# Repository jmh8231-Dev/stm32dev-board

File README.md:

# STM32F407ZETx 개발보드

**STM32F407ZETx** MCU를 중심으로 DS3231(RTC), VS1003(Audio Codec), microSD(4‑bit SDIO),
SN65HVD230(CAN), USB‑to‑TTL, **DP83848(Ethernet PHY)** 등을 온보드로 구성하고
대형 **브레드보드**와 12 V/5 V/3.3 V 전원 및 **SPI/I²C/PWM 헤더**를 둘러 배치한 실습·프로토타이핑 전용 보드입니다.

---

## 1. 보드 하이라이트

- **MCU**: STM32F407ZETx (LQFP‑144), 8/16 MHz 외부 크리스털, ST‑LINK 20‑핀
- **전원 트리**: 12 V DC 잭 입력 → **LM2596‑5 V**, **LM2596‑3.3 V**
  - 브레드보드 주변에 **12 V / 5 V / 3.3 V 전원 핀** 다수 제공
- **통신/네트워킹**
  - **DP83848** 10/100 Ethernet PHY + RJ45
  - **SN65HVD230** CAN 트랜시버
  - **USB‑to‑TTL**(FT232RL 계열)
- **저장/오디오/시간**
  - **microSD(4‑bit SDIO)**, **VS1003** 오디오 코덱, **DS3231 RTC**
- **사용자 입출력**
  - **20×4 캐릭터 LCD(CLCD2004)** 장착 영역(백라이트 제어)
  - **브레드보드** 장착(보드 일체), 주변에 **SPI/I²C/PWM 헤더** 배치
  - 가변저항/버튼/버저 등 실습용 풋프린트
- **확장성**: 각 인터페이스에 테스트 포인트/점퍼 제공

---

## 2. 주변장치 매핑 요약

| 기능 | 부품/모듈 | 인터페이스 | 비고 |
|---|---|---|---|
| Ethernet | TI **DP83848** | RMII/MII | RJ45, 링크 LED |
| CAN | TI **SN65HVD230** | CAN | 종단저항 점퍼 |
| Audio | **VS1003** | SPI / I²S | Sine test 지원 |
| Storage | microSD | **4‑bit SDIO** | 카드 감지/쓰기보호 |
| RTC | **DS3231** | I²C | 코인셀 백업 |
| USB‑UART | **FT232RL** | USB‑CDC | 부트 로그/쉘 |
| LCD | **CLCD2004** | 병렬 | 백라이트 제어 |
| Breadboard | 1열×2면 | — | SPI/I²C/PWM/전원 배치 |

---

## 3. 빠른 시작

1) 12 V 어댑터 연결 → 전원 LED 확인  
2) ST‑LINK 연결 후 예제 펌웨어 다운로드  
3) **Ethernet → CAN → SDIO → I²C(DS3231) → SPI(VS1003)** 순으로 브링업  
4) 브레드보드에 센서/액추에이터 연결 → SPI/I²C/PWM 헤더로 배선  
5) LCD 장착 후 상태/메뉴 표시 구현

---

## 4. 브링업 체크리스트

- **전원 리플/부하 테스트**(5 V/3.3 V)
- **SDIO 4‑bit**: HS 모드, 카드 감지/쓰기 보호 입력 확인
- **RMII/MII**: DP83848 링크/속도/MDIO 확인
- **CAN**: 루프백 → 실선 통신, 종단저항 설정
- **RTC**: DS3231 1 Hz/32 kHz, 온도 보정 레지스터 확인
- **VS1003**: SCI 레지스터 접근, sine test

---

## 5. 파일 트리

```text
stm32f407-devboard/
├─ README.md
└─ docs/
   └─ images/
      ├─ render_top.png
      ├─ pcb_layout.png
      └─ photo_top.jpg
```

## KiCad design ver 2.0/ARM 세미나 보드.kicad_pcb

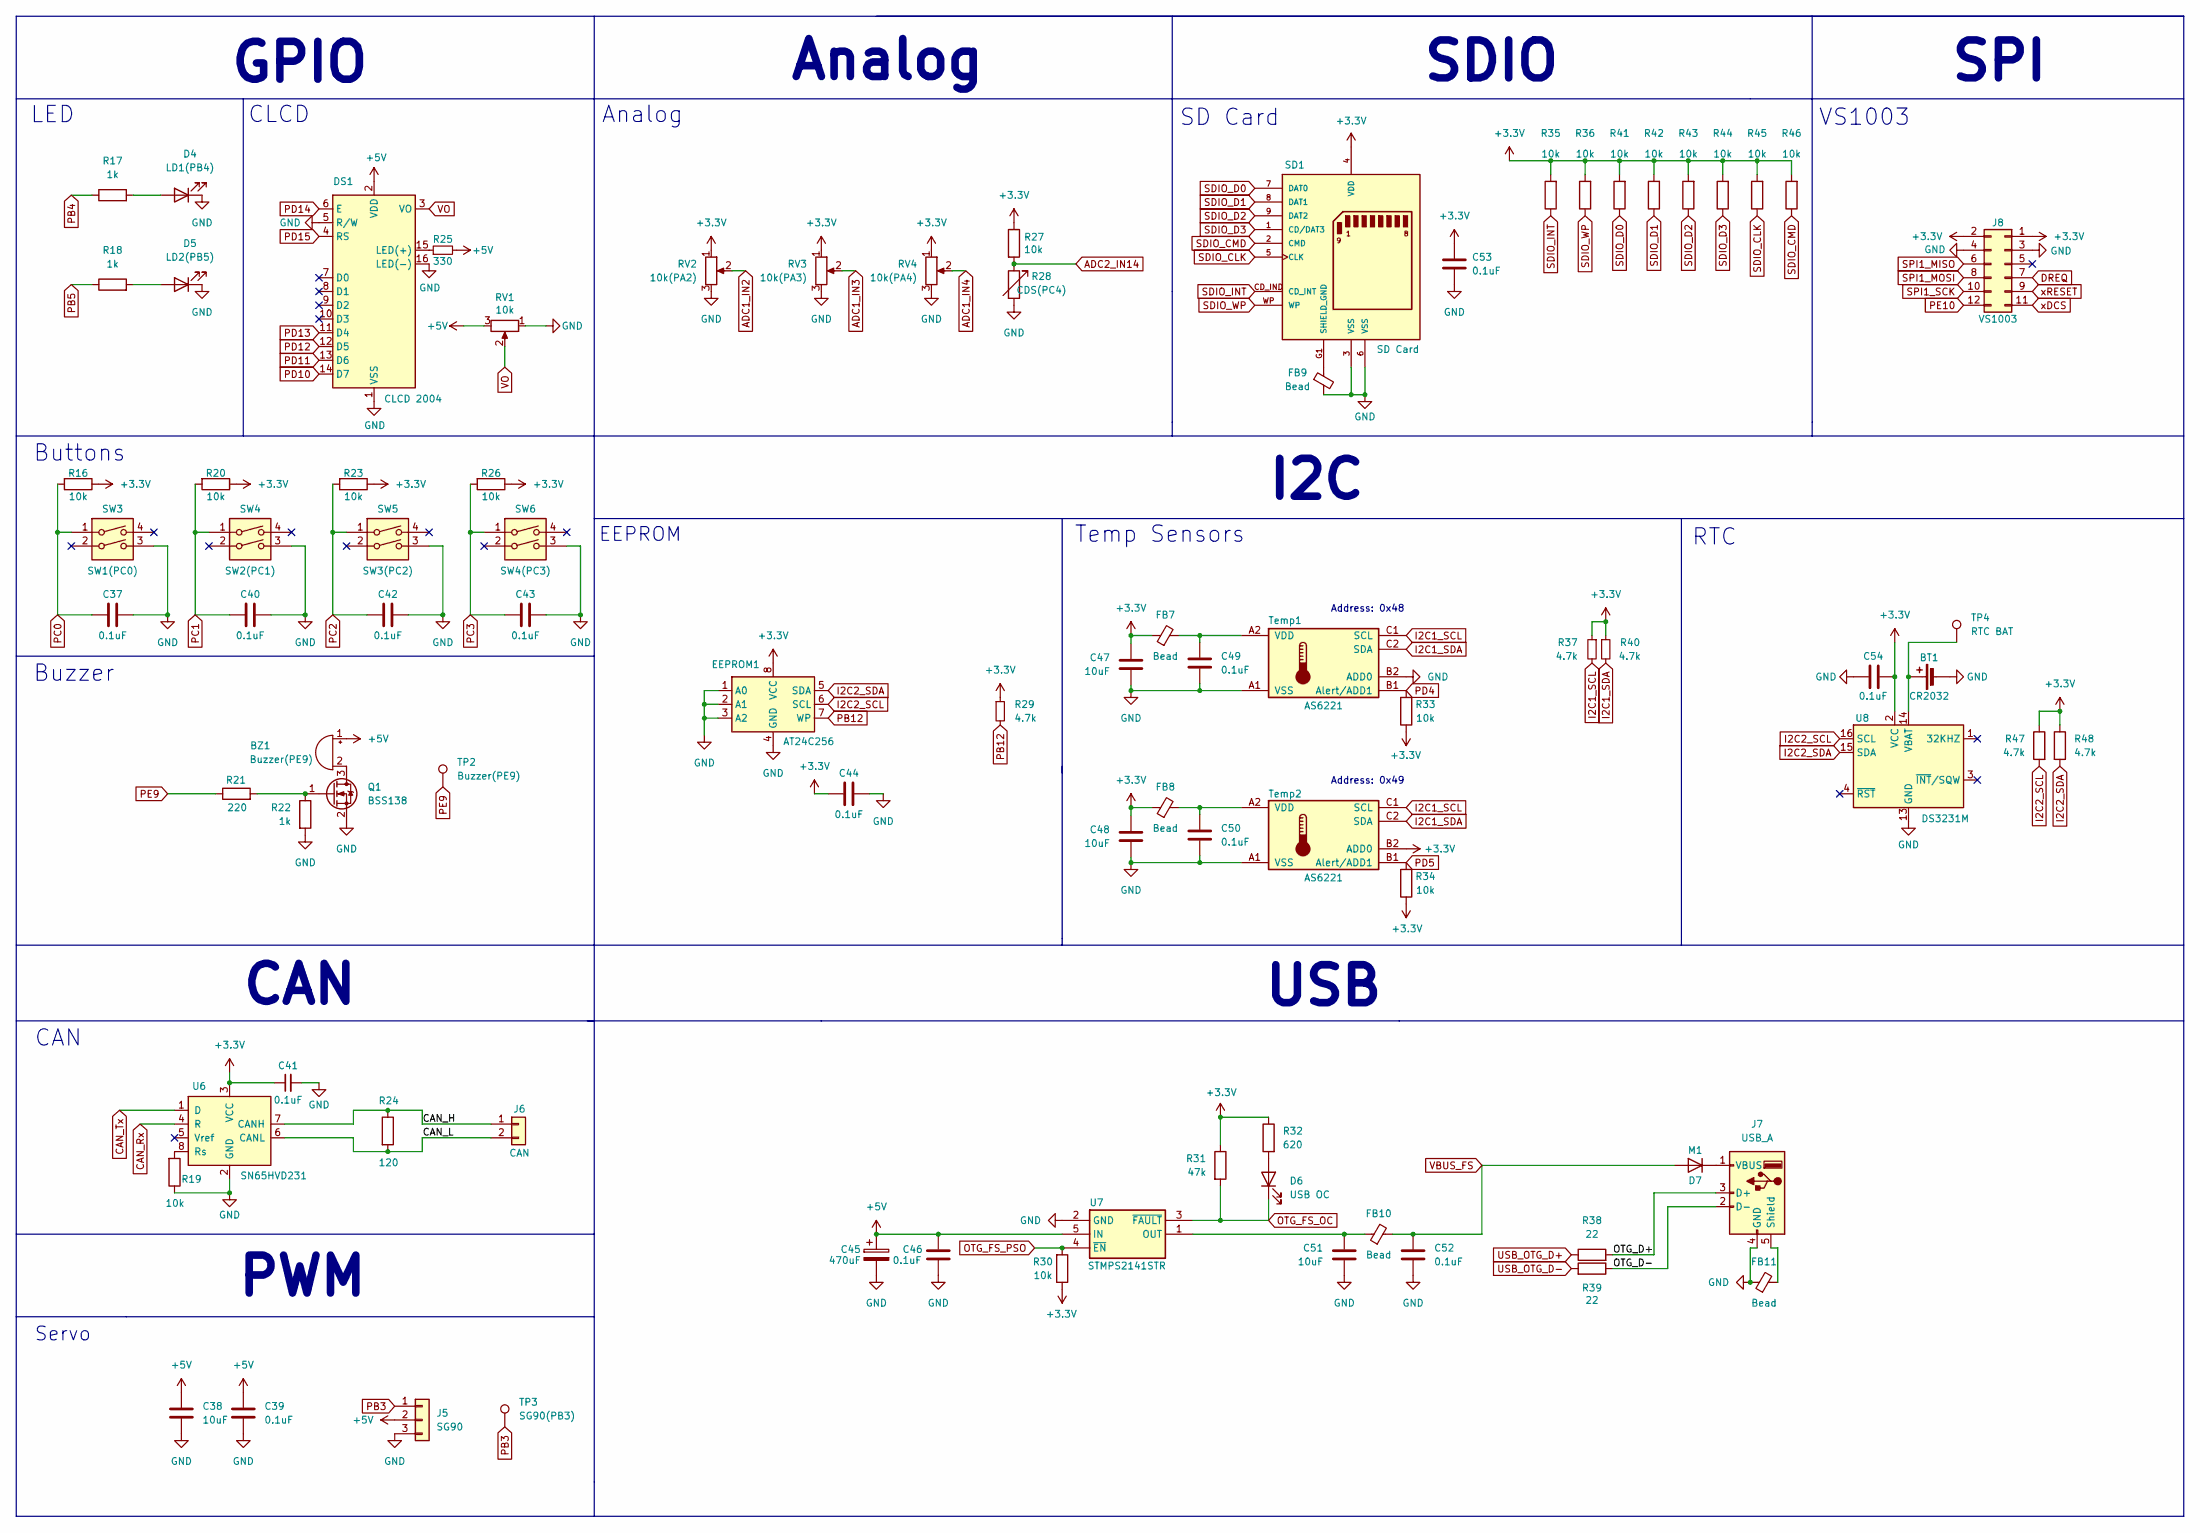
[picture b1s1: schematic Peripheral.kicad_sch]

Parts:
BT1: CR2032; BAT-HLD-001
BZ1: Buzzer(PE9); Buzzer_12x9.5RM7.6
C37, C39, C40, C41, C42, C43, C44, C46, C49, C50, C52, C53, C54: 0.1uF; C_0805_2012Metric
C38, C47, C48, C51: 10uF; C_1206_3216Metric
C45: 470uF; MVG25WV470M
D4: LD1(PB4); LED_0805_2012Metric
D5: LD2(PB5); LED_0805_2012Metric
D6: USB OC; LED_0805_2012Metric
D7: M1; D_SMA
DS1: CLCD 2004; LCD-20x4
EEPROM1: AT24C256; SOIC-8_3.9x4.9mm_P1.27mm
FB7, FB8, FB9, FB10, FB11: Bead; L_0805_2012Metric
J5: SG90; PinHeader_1x03_P2.54mm_Vertical
J6: CAN; PinHeader_1x02_P2.54mm_Vertical
J7: USB_A; USB_A_Connfly_DS1095
J8: VS1003; PinSocket_2x06_P2.54mm_Vertical
Q1: BSS138; SOT-23
R16, R19, R20, R23, R26, R27, R30, R33, R34, R35, R36, R41, R42, R43, R44, R45, R46: 10k; R_0805_2012Metric
R17, R18, R22: 1k; R_0805_2012Metric
R21: 220; R_0805_2012Metric
R24: 120; R_0805_2012Metric
R25: 330; R_0805_2012Metric
R28: CDS(PC4); R_LDR_5.0x4.1mm_P3mm_Vertical
R29, R37, R40, R47, R48: 4.7k; R_0805_2012Metric
R31: 47k; R_0805_2012Metric
R32: 620; R_0805_2012Metric
R38, R39: 22; R_0805_2012Metric
RV1: 10k; 3362P-103LF
RV2: 10k(PA2); RV09H20SQ-B10K
RV3: 10k(PA3); RV09H20SQ-B10K
RV4: 10k(PA4); RV09H20SQ-B10K
SD1: SD Card; AMPHENOL_GSD090012SEU; PARTREV E
SW3: SW1(PC0); SW_SMD_IT-1107
SW4: SW2(PC1); SW_SMD_IT-1107
SW5: SW3(PC2); SW_SMD_IT-1107
SW6: SW4(PC3); SW_SMD_IT-1107
TP2: Buzzer(PE9); TestPoint_Pad_D1.5mm
TP3: SG90(PB3); TestPoint_Pad_D1.5mm
TP4: RTC BAT; TestPoint_Pad_D1.5mm
Temp1, Temp2: AS6221; WLCSP-6_1.4x1.0mm_P0.4mm
U6: SN65HVD231; SOIC-8_3.9x4.9mm_P1.27mm
U7: STMPS2141STR; SOT-23-5
U8: DS3231M; SOIC-16W_7.5x10.3mm_P1.27mm

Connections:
+3.3V: C41.1, C44.1, C47.2, C48.2, C53.1, C54.2, EEPROM1.8 (VCC), FB7.1, FB8.1, J8.1, J8.2, R16.1, R20.1, R23.1, R26.1, R27.1, R29.1, R30.1, R31.1, R32.1, R33.1, R34.1, R35.2, R36.2, R37.1, R40.1, R41.2, R42.2, R43.2, R44.2, R45.2, R46.2, R47.1, R48.1, RV2.1, RV3.1, RV4.1, SD1.4 (VDD), Temp2.B2 (ADD0), U6.3 (VCC), U8.2 (VCC); also elsewhere on the board
+5V: BZ1.1 (+), C38.1, C39.1, C45.1, C46.1, DS1.2 (VDD), J5.2, R25.2, RV1.3, U7.5 (IN); also elsewhere on the board
/Peripheral/CAN_H: J6.1, R24.1, U6.7 (CANH)
/Peripheral/CAN_L: J6.2, R24.2, U6.6 (CANL)
/Peripheral/OTG_D+: J7.3 (D+), R38.2
/Peripheral/OTG_D-: J7.2 (D-), R39.1
ADC1_IN2: RV2.2; also elsewhere on the board
ADC1_IN3: RV3.2; also elsewhere on the board
ADC1_IN4: RV4.2; also elsewhere on the board
ADC2_IN14: R27.2, R28.1; also elsewhere on the board
CAN_Rx: U6.4 (R); also elsewhere on the board
CAN_Tx: U6.1 (D); also elsewhere on the board
DREQ: J8.7; also elsewhere on the board
GND: BT1.2 (-), C37.2, C38.2, C39.2, C40.2, C41.2, C42.2, C43.2, C44.2, C45.2, C46.2, C47.1, C48.1, C49.2, C50.2, C51.1, C52.2, C53.2, C54.1, D4.1 (K), D5.1 (K), DS1.1 (VSS), DS1.5 (R/W), DS1.16 (LED(-)), EEPROM1.1 (A0), EEPROM1.2 (A1), EEPROM1.3 (A2), EEPROM1.4 (GND), FB9.2, FB11.1, J5.3, J7.4 (GND), J8.3, J8.4, Q1.2 (S), R19.1, R22.2, R28.2, RV1.1, RV2.3, RV2.4, RV2.5, RV3.3, RV3.4, RV3.5, RV4.3, RV4.4, RV4.5, SD1.3 (VSS), SD1.6 (VSS), SW3.3, SW4.3, SW5.3, SW6.3, Temp1.A1 (VSS), Temp1.B2 (ADD0), Temp2.A1 (VSS), U6.2 (GND), U7.2 (GND), U8.5 (GND), U8.6 (GND), U8.7 (GND), U8.8 (GND), U8.9 (GND), U8.10 (GND), U8.11 (GND), U8.12 (GND), U8.13 (GND); also elsewhere on the board
I2C1_SCL: R37.2, Temp1.C1 (SCL), Temp2.C1 (SCL); also elsewhere on the board
I2C1_SDA: R40.2, Temp1.C2 (SDA), Temp2.C2 (SDA); also elsewhere on the board
I2C2_SCL: EEPROM1.6 (SCL), R47.2, U8.16 (SCL); also elsewhere on the board
I2C2_SDA: EEPROM1.5 (SDA), R48.2, U8.15 (SDA); also elsewhere on the board
unnamed: BT1.1 (+), TP4.1, U8.14 (VBAT)
unnamed: BZ1.2 (-), Q1.3 (D)
unnamed: D4.2 (A), R17.2
unnamed: D5.2 (A), R18.2
unnamed: D6.2 (A), R32.2
unnamed: D7.1 (K), J7.1 (VBUS)
unnamed: DS1.15 (LED(+)), R25.1
unnamed: FB11.2, J7.5 (Shield)
unnamed: Q1.1 (G), R21.2, R22.1
unnamed: C49.1, FB7.2, Temp1.A2 (VDD)
unnamed: C50.1, FB8.2, Temp2.A2 (VDD)
unnamed: R19.2, U6.8 (Rs)
unnamed: C51.2, FB10.1, U7.1 (OUT)
OTG_FS_OC: D6.1 (K), R31.2, U7.3 (~FAULT); also elsewhere on the board
OTG_FS_PSO: R30.2, U7.4 (~EN); also elsewhere on the board
PB3: J5.1, TP3.1; also elsewhere on the board
PB4: R17.1; also elsewhere on the board
PB5: R18.1; also elsewhere on the board
PB12: EEPROM1.7 (WP), R29.2; also elsewhere on the board
PC0: C37.1, R16.2, SW3.1; also elsewhere on the board
PC1: C40.1, R20.2, SW4.1; also elsewhere on the board
PC2: C42.1, R23.2, SW5.1; also elsewhere on the board
PC3: C43.1, R26.2, SW6.1; also elsewhere on the board
PD4: R33.2, Temp1.B1 (Alert/ADD1); also elsewhere on the board
PD5: R34.2, Temp2.B1 (Alert/ADD1); also elsewhere on the board
PD10: DS1.14 (D7); also elsewhere on the board
PD11: DS1.13 (D6); also elsewhere on the board
PD12: DS1.12 (D5); also elsewhere on the board
PD13: DS1.11 (D4); also elsewhere on the board
PD14: DS1.6 (E); also elsewhere on the board
PD15: DS1.4 (RS); also elsewhere on the board
PE9: R21.1, TP2.1; also elsewhere on the board
PE10: J8.12; also elsewhere on the board
SDIO_CLK: R45.1, SD1.5 (CLK); also elsewhere on the board
SDIO_CMD: R46.1, SD1.2 (CMD); also elsewhere on the board
SDIO_D0: R41.1, SD1.7 (DAT0); also elsewhere on the board
SDIO_D1: R42.1, SD1.8 (DAT1); also elsewhere on the board
SDIO_D2: R43.1, SD1.9 (DAT2); also elsewhere on the board
SDIO_D3: R44.1, SD1.1 (CD/DAT3); also elsewhere on the board
SDIO_INT: R35.1, SD1.CD_IND (CD_INT); also elsewhere on the board
SDIO_WP: R36.1, SD1.WP; also elsewhere on the board
SHIELD_GND: FB9.1, SD1.G1 (SHIELD_GND), SD1.G2 (SHIELD_GND), SD1.G3 (SHIELD_GND), SD1.G4 (SHIELD_GND)
SPI1_MISO: J8.6; also elsewhere on the board
SPI1_MOSI: J8.8; also elsewhere on the board
SPI1_SCK: J8.10; also elsewhere on the board
USB_OTG_D+: R38.1; also elsewhere on the board
USB_OTG_D-: R39.2; also elsewhere on the board
VBUS_FS: C52.1, D7.2 (A), FB10.2; also elsewhere on the board
VO: DS1.3 (VO), RV1.2
xDCS: J8.11; also elsewhere on the board
xRESET: J8.9; also elsewhere on the board

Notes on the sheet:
Address: 0x48
CLCD
Analog
Buttons
Buzzer
Servo
VS1003
RTC
EEPROM
LED
CAN
SPI
I2C
Temp Sensors
USB
SD Card
PWM
GPIO
SDIO
Address: 0x49

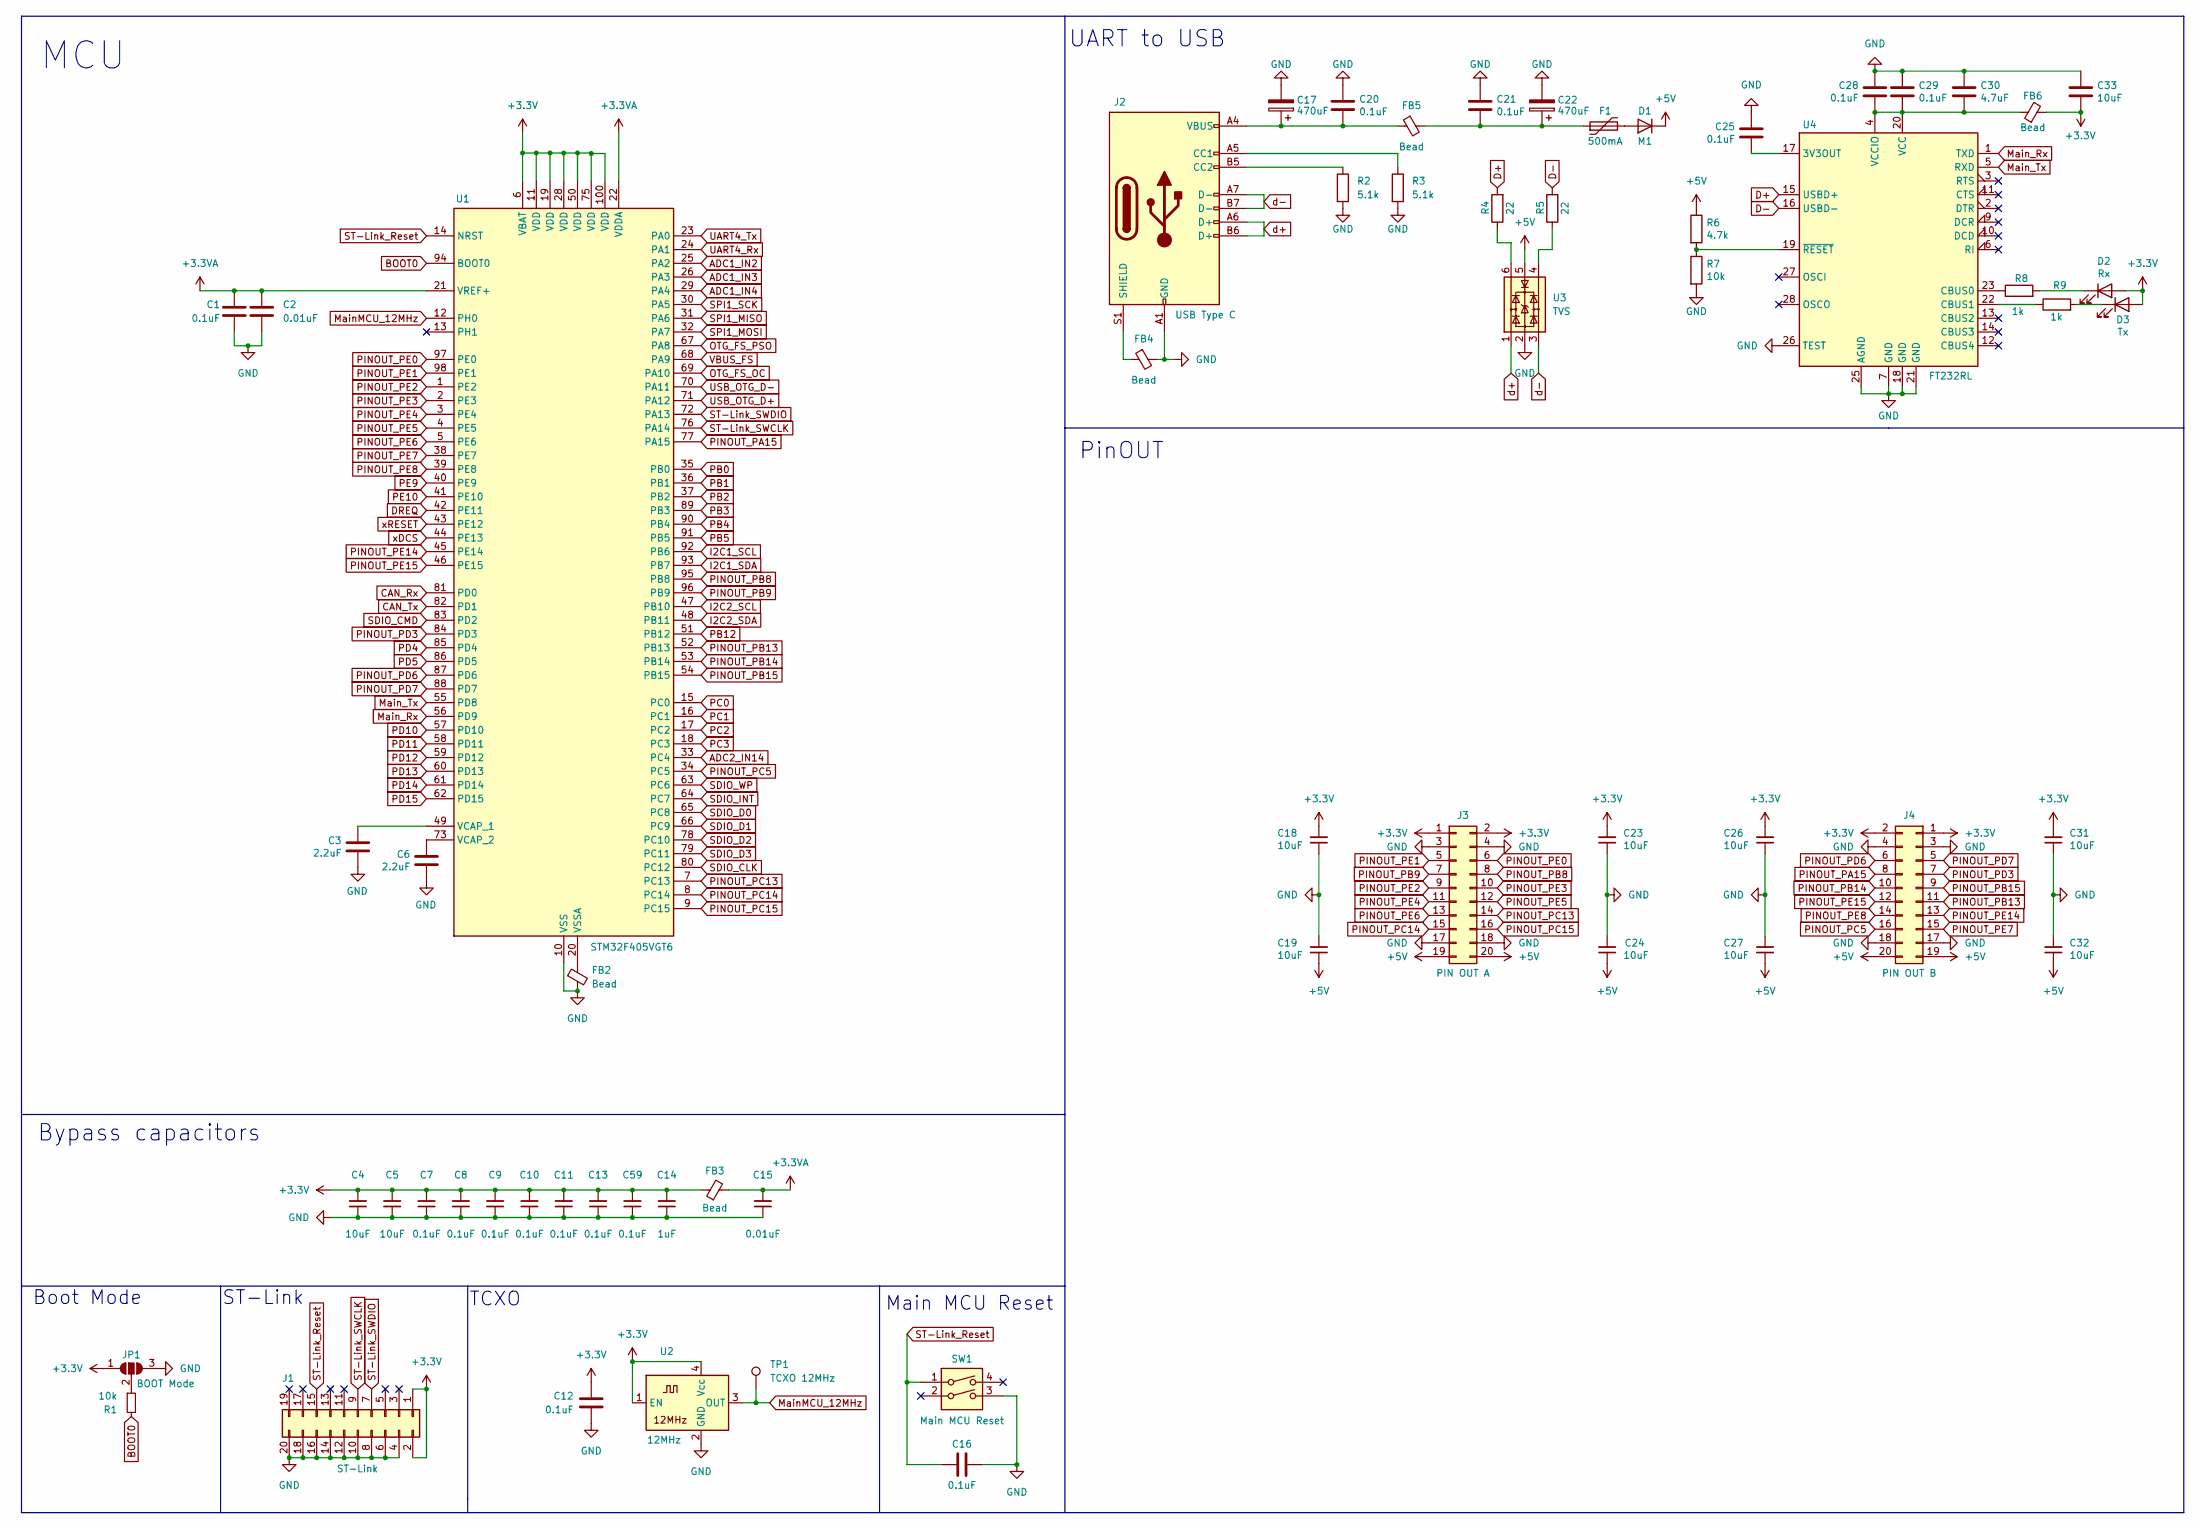
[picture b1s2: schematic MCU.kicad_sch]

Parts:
C1, C7, C8, C9, C10, C11, C12, C13, C16, C20, C21, C25, C28, C29, C59: 0.1uF; C_0805_2012Metric
C2, C15: 0.01uF; C_0805_2012Metric
C3, C6: 2.2uF; C_0805_2012Metric
C4, C5, C18, C19, C23, C24, C26, C27, C31, C32, C33: 10uF; C_1206_3216Metric
C14: 1uF; C_0805_2012Metric
C17, C22: 470uF; MVG25WV470M
C30: 4.7uF; C_0805_2012Metric
D1: M1; D_SMA
D2: Rx; LED_0805_2012Metric
D3: Tx; LED_0805_2012Metric
F1: 500mA; L_1210_3225Metric
FB2, FB3, FB4, FB5, FB6: Bead; L_0805_2012Metric
J1: ST-Link; IDC-Header_2x10_P2.54mm_Vertical
J2: USB Type C; USB_C_Receptacle_HRO_TYPE-C-31-M-12
J3: PIN OUT A; PinHeader_2x10_P2.54mm_Vertical
J4: PIN OUT B; PinHeader_2x10_P2.54mm_Vertical
JP1: BOOT Mode; SolderJumper-3_P1.3mm_Open_RoundedPad1.0x1.5mm
R1, R7: 10k; R_0805_2012Metric
R2, R3: 5.1k; R_0805_2012Metric
R4, R5: 22; R_0805_2012Metric
R6: 4.7k; R_0805_2012Metric
R8, R9: 1k; R_0805_2012Metric
SW1: Main MCU Reset; SW_SMD_IT-1107
TP1: TCXO 12MHz; TestPoint_Pad_D1.5mm
U1: STM32F405VGT6; LQFP-100_14x14mm_P0.5mm
U2: 12MHz; ECS-TXO-2016
U3: TVS; SOT-23-6
U4: FT232RL; SSOP-28_5.3x10.2mm_P0.65mm

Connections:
+3.3V: C4.2, C5.2, C7.2, C8.2, C9.2, C10.2, C11.2, C12.1, C13.2, C14.2, C18.2, C23.2, C26.2, C31.2, C33.1, C59.2, D2.2 (A), D3.2 (A), FB3.1, FB6.2, J1.1, J1.2, J3.1, J3.2, J4.1, J4.2, JP1.1 (A), U1.6 (VBAT), U1.11 (VDD), U1.19 (VDD), U1.28 (VDD), U1.50 (VDD), U1.75 (VDD), U1.100 (VDD), U2.1 (EN), U2.4 (Vcc); also elsewhere on the board
+3.3VA: C1.2, C2.2, C15.2, FB3.2, U1.21 (VREF+), U1.22 (VDDA)
+5V: C19.1, C24.1, C27.1, C32.1, D1.1 (K), J3.19, J3.20, J4.19, J4.20, R6.1, U3.5; also elsewhere on the board
ADC1_IN2: U1.25 (PA2); also elsewhere on the board
ADC1_IN3: U1.26 (PA3); also elsewhere on the board
ADC1_IN4: U1.29 (PA4); also elsewhere on the board
ADC2_IN14: U1.33 (PC4); also elsewhere on the board
BOOT0: R1.2, U1.94 (BOOT0)
CAN_Rx: U1.81 (PD0); also elsewhere on the board
CAN_Tx: U1.82 (PD1); also elsewhere on the board
D+: R4.2, U4.15 (USBD+)
D-: R5.2, U4.16 (USBD-)
DREQ: U1.42 (PE11); also elsewhere on the board
GND: C1.1, C2.1, C3.2, C4.1, C5.1, C6.2, C7.1, C8.1, C9.1, C10.1, C11.1, C12.2, C13.1, C14.1, C15.1, C16.2, C17.2, C18.1, C19.2, C20.2, C21.2, C22.2, C23.1, C24.2, C25.2, C26.1, C27.2, C28.2, C29.2, C30.2, C31.1, C32.2, C33.2, C59.1, FB2.2, FB4.2, J1.4, J1.6, J1.8, J1.10, J1.12, J1.14, J1.16, J1.18, J1.20, J2.A1 (GND), J2.A12 (GND), J2.B1 (GND), J2.B12 (GND), J3.3, J3.4, J3.17, J3.18, J4.3, J4.4, J4.17, J4.18, JP1.3 (B), R2.2, R3.2, R7.2, SW1.3, U1.10 (VSS), U1.27 (VSS), U1.74 (VSS), U1.99 (VSS), U2.2 (GND), U3.2, U4.7 (GND), U4.18 (GND), U4.21 (GND), U4.25 (AGND), U4.26 (TEST); also elsewhere on the board
I2C1_SCL: U1.92 (PB6); also elsewhere on the board
I2C1_SDA: U1.93 (PB7); also elsewhere on the board
I2C2_SCL: U1.47 (PB10); also elsewhere on the board
I2C2_SDA: U1.48 (PB11); also elsewhere on the board
MainMCU_12MHz: TP1.1, U1.12 (PH0), U2.3 (OUT)
Main_Rx: U1.56 (PD9), U4.1 (TXD)
Main_Tx: U1.55 (PD8), U4.5 (RXD)
unnamed: C17.1, C20.1, FB5.1, J2.A4 (VBUS), J2.A9 (VBUS), J2.B4 (VBUS), J2.B9 (VBUS)
unnamed: C21.1, C22.1, F1.1, FB5.2
unnamed: D1.2 (A), F1.2
unnamed: D2.1 (K), R8.2
unnamed: D3.1 (K), R9.2
unnamed: J2.A5 (CC1), R3.1
unnamed: J2.B5 (CC2), R2.1
unnamed: FB4.1, J2.S1 (SHIELD)
unnamed: JP1.2 (C), R1.1
unnamed: R4.1, U3.6
unnamed: R5.1, U3.4
unnamed: C3.1, U1.49 (VCAP_1)
unnamed: C6.1, U1.73 (VCAP_2)
unnamed: FB2.1, U1.20 (VSSA)
unnamed: C25.1, U4.17 (3V3OUT)
unnamed: R8.1, U4.23 (CBUS0)
unnamed: R9.1, U4.22 (CBUS1)
unnamed: C28.1, C29.1, C30.1, FB6.1, U4.4 (VCCIO), U4.20 (VCC)
unnamed: R6.2, R7.1, U4.19 (~RESET)
OTG_FS_OC: U1.69 (PA10); also elsewhere on the board
OTG_FS_PSO: U1.67 (PA8); also elsewhere on the board
PB0: U1.35 (PB0); also elsewhere on the board
PB1: U1.36 (PB1); also elsewhere on the board
PB2: U1.37 (PB2); also elsewhere on the board
PB3: U1.89 (PB3); also elsewhere on the board
PB4: U1.90 (PB4); also elsewhere on the board
PB5: U1.91 (PB5); also elsewhere on the board
PB12: U1.51 (PB12); also elsewhere on the board
PC0: U1.15 (PC0); also elsewhere on the board
PC1: U1.16 (PC1); also elsewhere on the board
PC2: U1.17 (PC2); also elsewhere on the board
PC3: U1.18 (PC3); also elsewhere on the board
PD4: U1.85 (PD4); also elsewhere on the board
PD5: U1.86 (PD5); also elsewhere on the board
PD10: U1.57 (PD10); also elsewhere on the board
PD11: U1.58 (PD11); also elsewhere on the board
PD12: U1.59 (PD12); also elsewhere on the board
PD13: U1.60 (PD13); also elsewhere on the board
PD14: U1.61 (PD14); also elsewhere on the board
PD15: U1.62 (PD15); also elsewhere on the board
PE9: U1.40 (PE9); also elsewhere on the board
PE10: U1.41 (PE10); also elsewhere on the board
PINOUT_PA15: J4.8, U1.77 (PA15)
PINOUT_PB8: J3.8, U1.95 (PB8)
PINOUT_PB9: J3.7, U1.96 (PB9)
PINOUT_PB13: J4.11, U1.52 (PB13)
PINOUT_PB14: J4.10, U1.53 (PB14)
PINOUT_PB15: J4.9, U1.54 (PB15)
PINOUT_PC5: J4.16, U1.34 (PC5)
PINOUT_PC13: J3.14, U1.7 (PC13)
PINOUT_PC14: J3.15, U1.8 (PC14)
PINOUT_PC15: J3.16, U1.9 (PC15)
PINOUT_PD3: J4.7, U1.84 (PD3)
PINOUT_PD6: J4.6, U1.87 (PD6)
PINOUT_PD7: J4.5, U1.88 (PD7)
PINOUT_PE0: J3.6, U1.97 (PE0)
PINOUT_PE1: J3.5, U1.98 (PE1)
PINOUT_PE2: J3.9, U1.1 (PE2)
PINOUT_PE3: J3.10, U1.2 (PE3)
PINOUT_PE4: J3.11, U1.3 (PE4)
PINOUT_PE5: J3.12, U1.4 (PE5)
PINOUT_PE6: J3.13, U1.5 (PE6)
PINOUT_PE7: J4.15, U1.38 (PE7)
PINOUT_PE8: J4.14, U1.39 (PE8)
PINOUT_PE14: J4.13, U1.45 (PE14)
PINOUT_PE15: J4.12, U1.46 (PE15)
SDIO_CLK: U1.80 (PC12); also elsewhere on the board
SDIO_CMD: U1.83 (PD2); also elsewhere on the board
SDIO_D0: U1.65 (PC8); also elsewhere on the board
SDIO_D1: U1.66 (PC9); also elsewhere on the board
SDIO_D2: U1.78 (PC10); also elsewhere on the board
SDIO_D3: U1.79 (PC11); also elsewhere on the board
SDIO_INT: U1.64 (PC7); also elsewhere on the board
SDIO_WP: U1.63 (PC6); also elsewhere on the board
SPI1_MISO: U1.31 (PA6); also elsewhere on the board
SPI1_MOSI: U1.32 (PA7); also elsewhere on the board
SPI1_SCK: U1.30 (PA5); also elsewhere on the board
ST-Link_Reset: C16.1, J1.15, SW1.1, U1.14 (NRST)
ST-Link_SWCLK: J1.9, U1.76 (PA14)
ST-Link_SWDIO: J1.7, U1.72 (PA13)
UART4_Rx: U1.24 (PA1); also elsewhere on the board
UART4_Tx: U1.23 (PA0); also elsewhere on the board
USB_OTG_D+: U1.71 (PA12); also elsewhere on the board
USB_OTG_D-: U1.70 (PA11); also elsewhere on the board
VBUS_FS: U1.68 (PA9); also elsewhere on the board
d+: J2.A6 (D+), J2.B6 (D+), U3.1
d-: J2.A7 (D-), J2.B7 (D-), U3.3
xDCS: U1.44 (PE13); also elsewhere on the board
xRESET: U1.43 (PE12); also elsewhere on the board

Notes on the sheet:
UART to USB
Bypass capacitors
TCXO
MCU
Main MCU Reset
Boot Mode
ST-Link
PinOUT

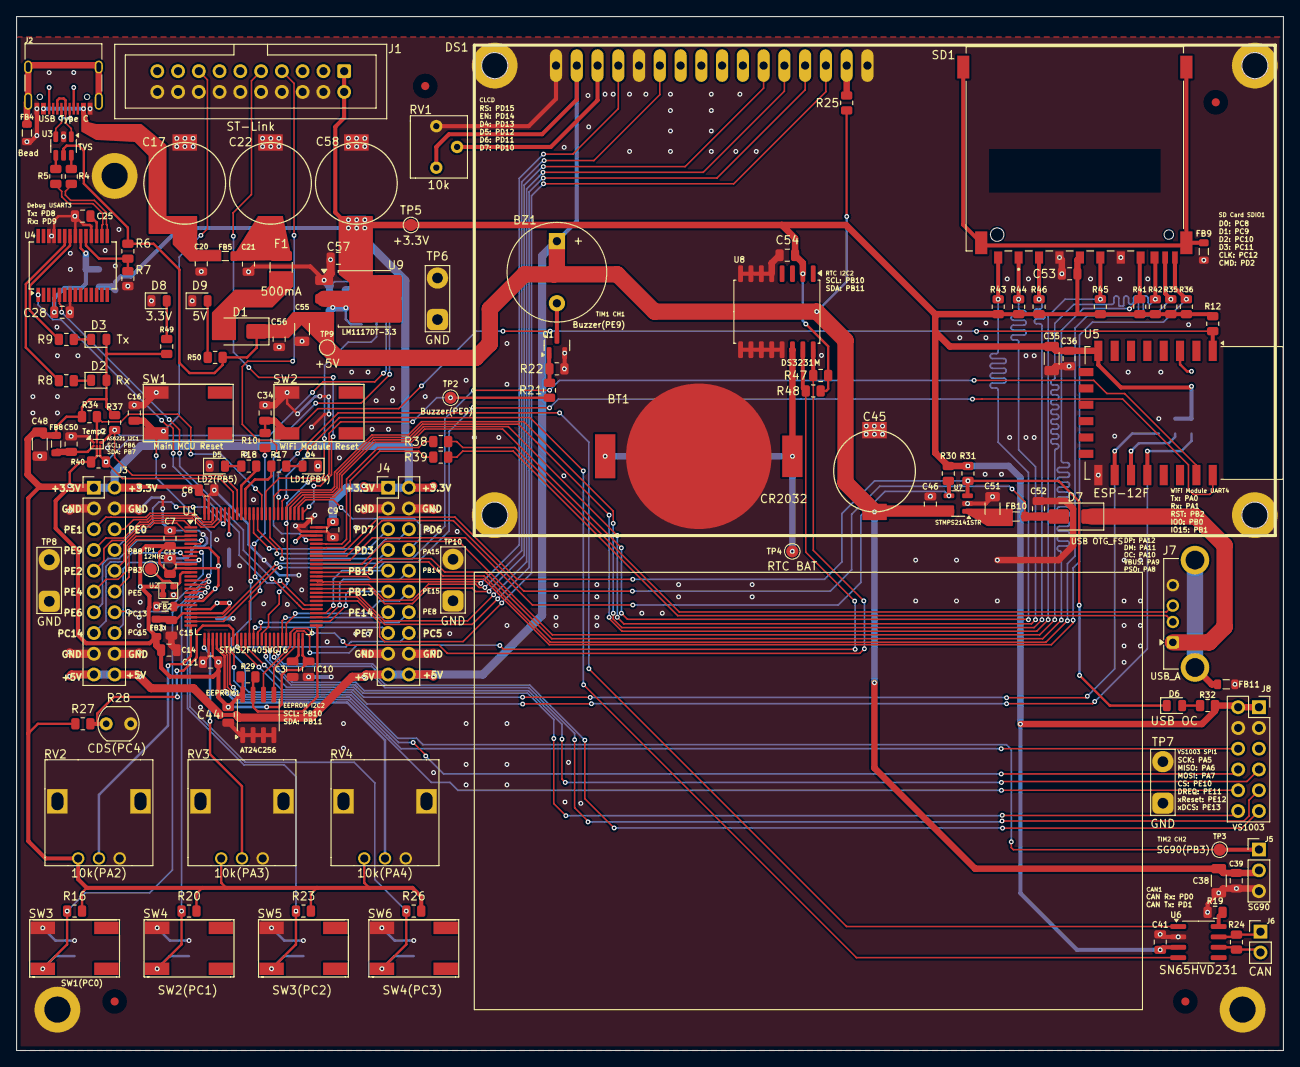
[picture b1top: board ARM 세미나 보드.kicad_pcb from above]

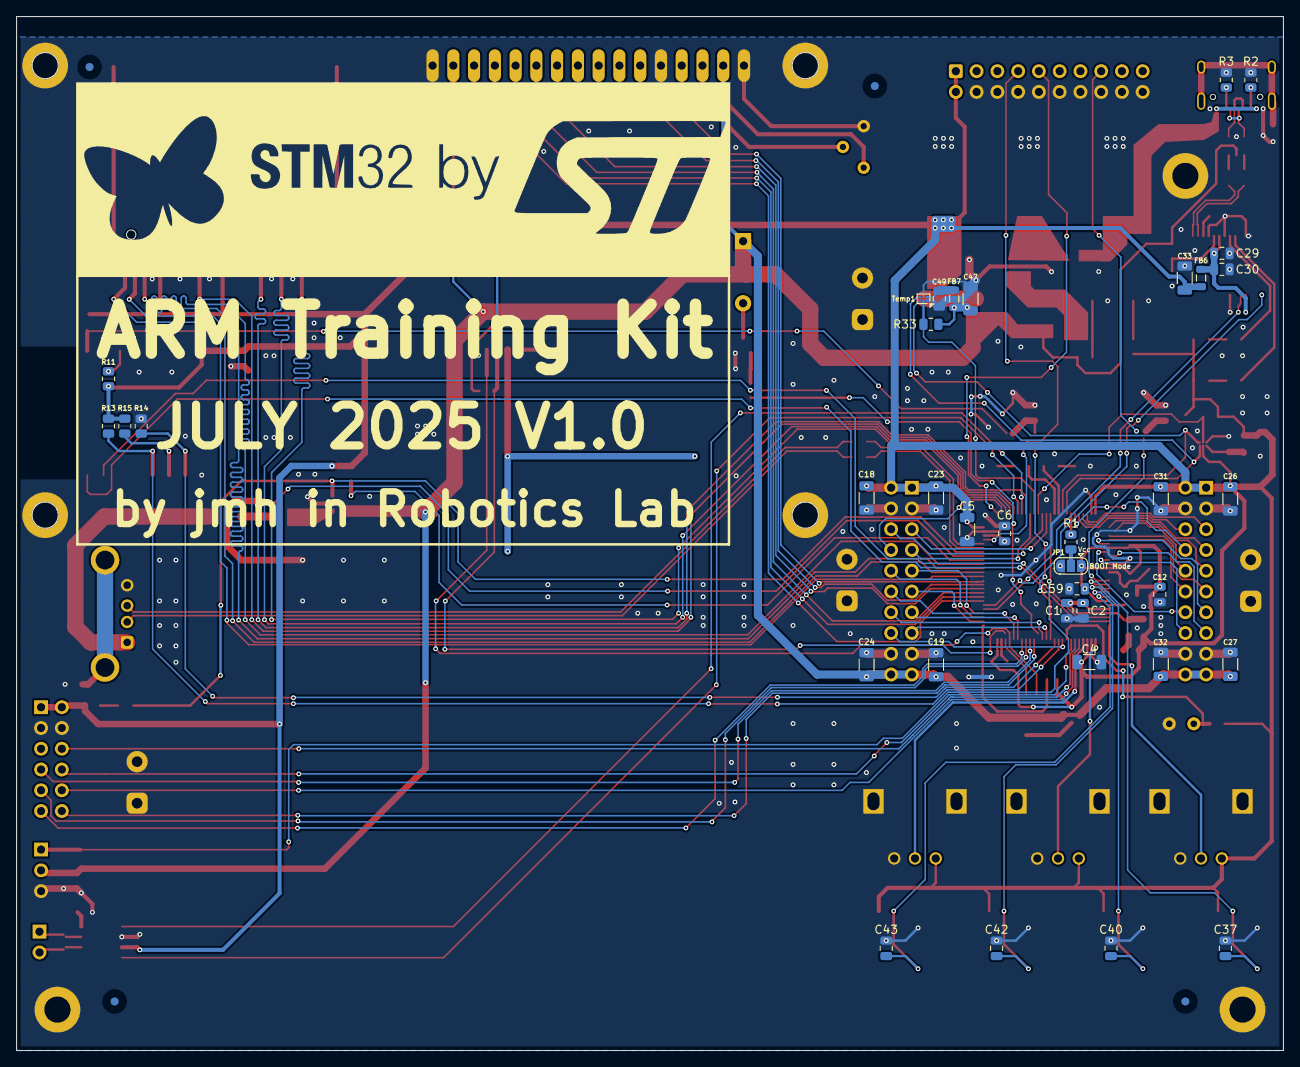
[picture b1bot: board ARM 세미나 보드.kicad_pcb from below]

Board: 2 copper layers, 155.0 x 126.5 mm, 175 parts (36 on the bottom side), 134 nets.

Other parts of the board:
C34, C36, C56, C57: 0.1uF; C_0805_2012Metric
C35, C55: 10uF; C_1206_3216Metric
C58: 470uF; MVG25WV470M
D8: 3.3V; LED_0805_2012Metric
D9: 5V; LED_0805_2012Metric
R10, R11, R12, R13, R14, R15, R50: 10k; R_0805_2012Metric
R49: 1k; R_0805_2012Metric
SW2: WiFi Module Reset; SW_SMD_IT-1107
TP5: +3.3V; TestPoint_Pad_D1.5mm
TP6, TP7, TP8, TP10: GND; TestPoint_2Pads_Pitch5.08mm_Drill1.3mm
TP9: +5V; TestPoint_Pad_D1.5mm
U5: ESP-12F; ESP-12E
U9: LM1117DT-3.3; TO-252-3_TabPin2

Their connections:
+3.3V: C35.2, C36.2, C57.2, C58.1, R11.1, R12.1, R13.2, R15.1, R49.2, TP5.1, U5.8 (VCC), U9.2 (VO); also elsewhere on the board
+5V: C55.2, C56.2, R50.2, TP9.1, U9.3 (VI); also elsewhere on the board
ESP8266_Reset: C34.1, R10.2, R12.2, SW2.1, U5.1 (~RST)
GND: C34.2, C35.1, C36.1, C55.1, C56.1, C57.1, C58.2, D8.1 (K), D9.1 (K), R14.1, SW2.3, TP6.1, TP6.2, TP7.1, TP7.2, TP8.1, TP8.2, TP10.1, TP10.2, U5.15 (GND), U9.1 (GND); also elsewhere on the board
unnamed: D8.2 (A), R49.1
unnamed: D9.2 (A), R50.1
unnamed: R11.2, U5.3 (EN)
unnamed: R15.2, U5.17 (GPIO2)
PB0: R13.1, U5.18 (GPIO0); also elsewhere on the board
PB1: R14.2, U5.16 (GPIO15); also elsewhere on the board
PB2: R10.1; also elsewhere on the board
UART4_Rx: U5.22 (GPIO1/TXD); also elsewhere on the board
UART4_Tx: U5.21 (GPIO3/RXD); also elsewhere on the board
